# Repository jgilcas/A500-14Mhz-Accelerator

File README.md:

# A500-14Mhz-Accelerator

Updated version of the infamous 14Mhz Accelerator by Livio Plos - stackable with the 8MB FastRAM board. 

Yeah i know, there's a load of accelerators out there (the TF520/530/534 by the exceptionally talented Stephen 'TerribleFire' Leary being the most prominent) that are much, much more impressive than this - but this has the following things going for it:

1) It's 100% through hole soldering, no SMT parts - easy for a beginner or for someone with shaky hands like me.
2) It's cheap to build
3) Uses simple logic gates - no fancy-schmancy CPLD/FPGA gubbins ;)
4) It's...err...it's...it's green (well, it can be if you choose that colour solder mask!)

Stacking with the 8MB FastRAM board works a treat although clearance with the top case in an A500 miiiiight be an issue. 

Uses 68HC000 chips, these run a lot cooler than the originals, and can be clocked high, without the need of a heatsink.

# Bill of Materials

--== COMING SOON ==--

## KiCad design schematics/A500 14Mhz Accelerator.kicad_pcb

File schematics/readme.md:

No special footprints or libraries required - standard KiCad libraries will suffice.

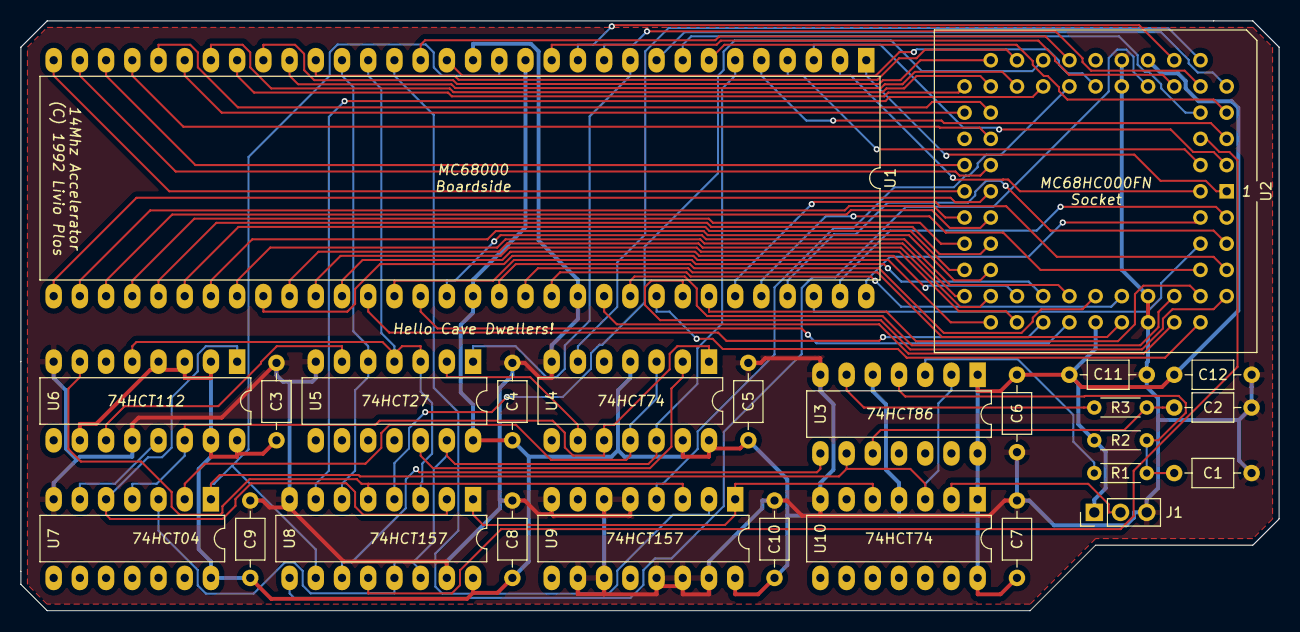
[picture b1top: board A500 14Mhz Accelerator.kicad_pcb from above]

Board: 2 copper layers, 121.9 x 57.1 mm, 26 parts (0 on the bottom side), 83 nets.

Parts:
C1, C2: 22pf; C_Axial_L3.8mm_D2.6mm_P7.50mm_Horizontal
C3, C4, C5, C6, C7, C8, C9, C10, C11, C12: 0.1uF; C_Axial_L3.8mm_D2.6mm_P7.50mm_Horizontal
J1: Speed Selector; PinHeader_1x03_P2.54mm_Vertical
R1, R3: 560; R_Axial_DIN0204_L3.6mm_D1.6mm_P5.08mm_Horizontal
R2: 10k; R_Axial_DIN0204_L3.6mm_D1.6mm_P5.08mm_Horizontal
U1: 68000 Boardside; DIP-64_W22.86mm_LongPads
U2: 68HC000 Socket; PLCC-68_THT-Socket
U3: 74HC86; DIP-14_W7.62mm_LongPads
U4, U10: 74HC74; DIP-14_W7.62mm_LongPads
U5: 74LS27; DIP-14_W7.62mm_LongPads
U6: 74LS112; DIP-16_W7.62mm_LongPads
U7: 74HC04; DIP-14_W7.62mm_LongPads
U8, U9: 74LS157; DIP-16_W7.62mm_LongPads

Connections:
/A500 14Mhz Accelerator Sheet 2/CDAC: C2.2, R3.1, U3.10
/A500 14Mhz Accelerator Sheet 2/SEL_SW: U8.1, U9.1, U10.5
/A500 14Mhz Accelerator Sheet 2/SPD_SEL: J1.2, U10.2
/A500 14Mhz Accelerator Sheet 2/SW_CLK14: U3.8, U8.11
/A500 14Mhz Accelerator Sheet 2/SW_E14: U6.1, U7.5, U8.2
/A500 14Mhz Accelerator Sheet 2/SW_VMA: U6.7, U8.5, U9.3
/A500 14Mhz Accelerator Sheet 2/_CLKIN: U4.3, U4.11, U7.2
/A500 14Mhz Accelerator Sheet 2/_E_OUT: U6.13, U7.6
/CPU_A1: U1.29, U2.32
/CPU_A2: U1.30, U2.33
/CPU_A3: U1.31, U2.34
/CPU_A4: U1.32, U2.35
/CPU_A5: U1.33, U2.36
/CPU_A6: U1.34, U2.37
/CPU_A7: U1.35, U2.38
/CPU_A8: U1.36, U2.39
/CPU_A9: U1.37, U2.40
/CPU_A10: U1.38, U2.41
/CPU_A11: U1.39, U2.42
/CPU_A12: U1.40, U2.43
/CPU_A13: U1.41, U2.44
/CPU_A14: U1.42, U2.45
/CPU_A15: U1.43, U2.46
/CPU_A16: U1.44, U2.47
/CPU_A17: U1.45, U2.48
/CPU_A18: U1.46, U2.49
/CPU_A19: U1.47, U2.50
/CPU_A20: U1.48, U2.51
/CPU_A21: U1.50, U2.53
/CPU_A22: U1.51, U2.54
/CPU_A23: U1.52, U2.55
/CPU_AS: U1.6, U4.12, U5.13, U7.3, U8.13, U8.14
/CPU_AS14: U2.6, U8.12
/CPU_BERR: U1.22, U2.24
/CPU_BG: U1.11, U2.11
/CPU_BGACK: U1.12, U2.12
/CPU_BR: U1.13, U2.13
/CPU_CLK: U1.15, U3.2, U3.9, U7.1, U8.10, U10.3
/CPU_CLK14: U2.15, U8.9
/CPU_D0: U1.5, U2.5
/CPU_D1: U1.4, U2.4
/CPU_D2: U1.3, U2.3
/CPU_D3: U1.2, U2.2
/CPU_D4: U1.1, U2.1
/CPU_D5: U1.64, U2.68
/CPU_D6: U1.63, U2.67
/CPU_D7: U1.62, U2.66
/CPU_D8: U1.61, U2.65
/CPU_D9: U1.60, U2.64
/CPU_D10: U1.59, U2.63
/CPU_D11: U1.58, U2.62
/CPU_D12: U1.57, U2.61
/CPU_D13: U1.56, U2.60
/CPU_D14: U1.55, U2.59
/CPU_D15: U1.54, U2.58
/CPU_DTACK: U1.10, U5.1
/CPU_DTACK14: U2.10, U4.6
/CPU_E: U1.20, U5.3, U5.4, U6.5, U8.3
/CPU_E14: U2.22, U8.4
/CPU_FC0: U1.28, U2.30
/CPU_FC1: U1.27, U2.29
/CPU_FC2: U1.26, U2.28
/CPU_HALT: U1.17, U2.19
/CPU_IPL0: U1.25, U2.27
/CPU_IPL1: U1.24, U2.26
/CPU_IPL2: U1.23, U2.25
/CPU_LDS: U1.8, U2.8
/CPU_RESET: U1.18, U2.20
/CPU_RW: U1.9, U2.9
/CPU_UDS: U1.7, U2.7
/CPU_VMA: U1.19, U9.2
/CPU_VMA14: U2.21, U9.4
/CPU_VPA: U1.21, U5.5, U8.6
/CPU_VPA14: U2.23, U8.7
/GND: C1.1, C2.1, C3.2, C4.2, C5.2, C6.2, C7.2, C8.2, C9.2, C10.2, C11.2, C12.2, J1.3, U1.16, U1.53, U2.16, U2.17, U2.56, U2.57, U3.7, U4.7, U5.7, U6.8, U6.12, U7.7, U8.8, U8.15, U9.5, U9.6, U9.8, U9.10, U9.11, U9.13, U9.14, U9.15, U10.7
/VCC: C3.1, C4.1, C5.1, C6.1, C7.1, C8.1, C9.1, C10.1, C11.1, C12.1, J1.1, R2.1, U1.14, U1.49, U2.14, U2.52, U3.1, U3.5, U3.14, U4.4, U4.13, U4.14, U5.14, U6.2, U6.3, U6.4, U6.10, U6.15, U6.16, U7.14, U8.16, U9.16, U10.1, U10.4, U10.14
unnamed: C1.2, R1.1, R2.2, U3.4
unnamed: R1.2, U3.3
unnamed: R3.2, U3.6
unnamed: U4.1, U4.10, U6.14, U7.4
unnamed: U4.2, U5.12
unnamed: U4.9, U5.2
unnamed: U5.6, U6.11

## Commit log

2019-05-26 Add files via upload
    Update the silkscreen
2019-06-06 Respin to add copper fill
    Moved components around for better decoupling on the caps, added copper fill
2019-06-08 Re-doing the copper fill
2019-06-11 Reroute with correct socket

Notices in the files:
schematics/A500 14Mhz Accelerator.kicad_pcb:
(C) 1992 Livio Plos
